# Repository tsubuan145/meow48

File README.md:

Build guide(Japanese only)
https://note.com/tsubuan_145/n/n66479057b7cb

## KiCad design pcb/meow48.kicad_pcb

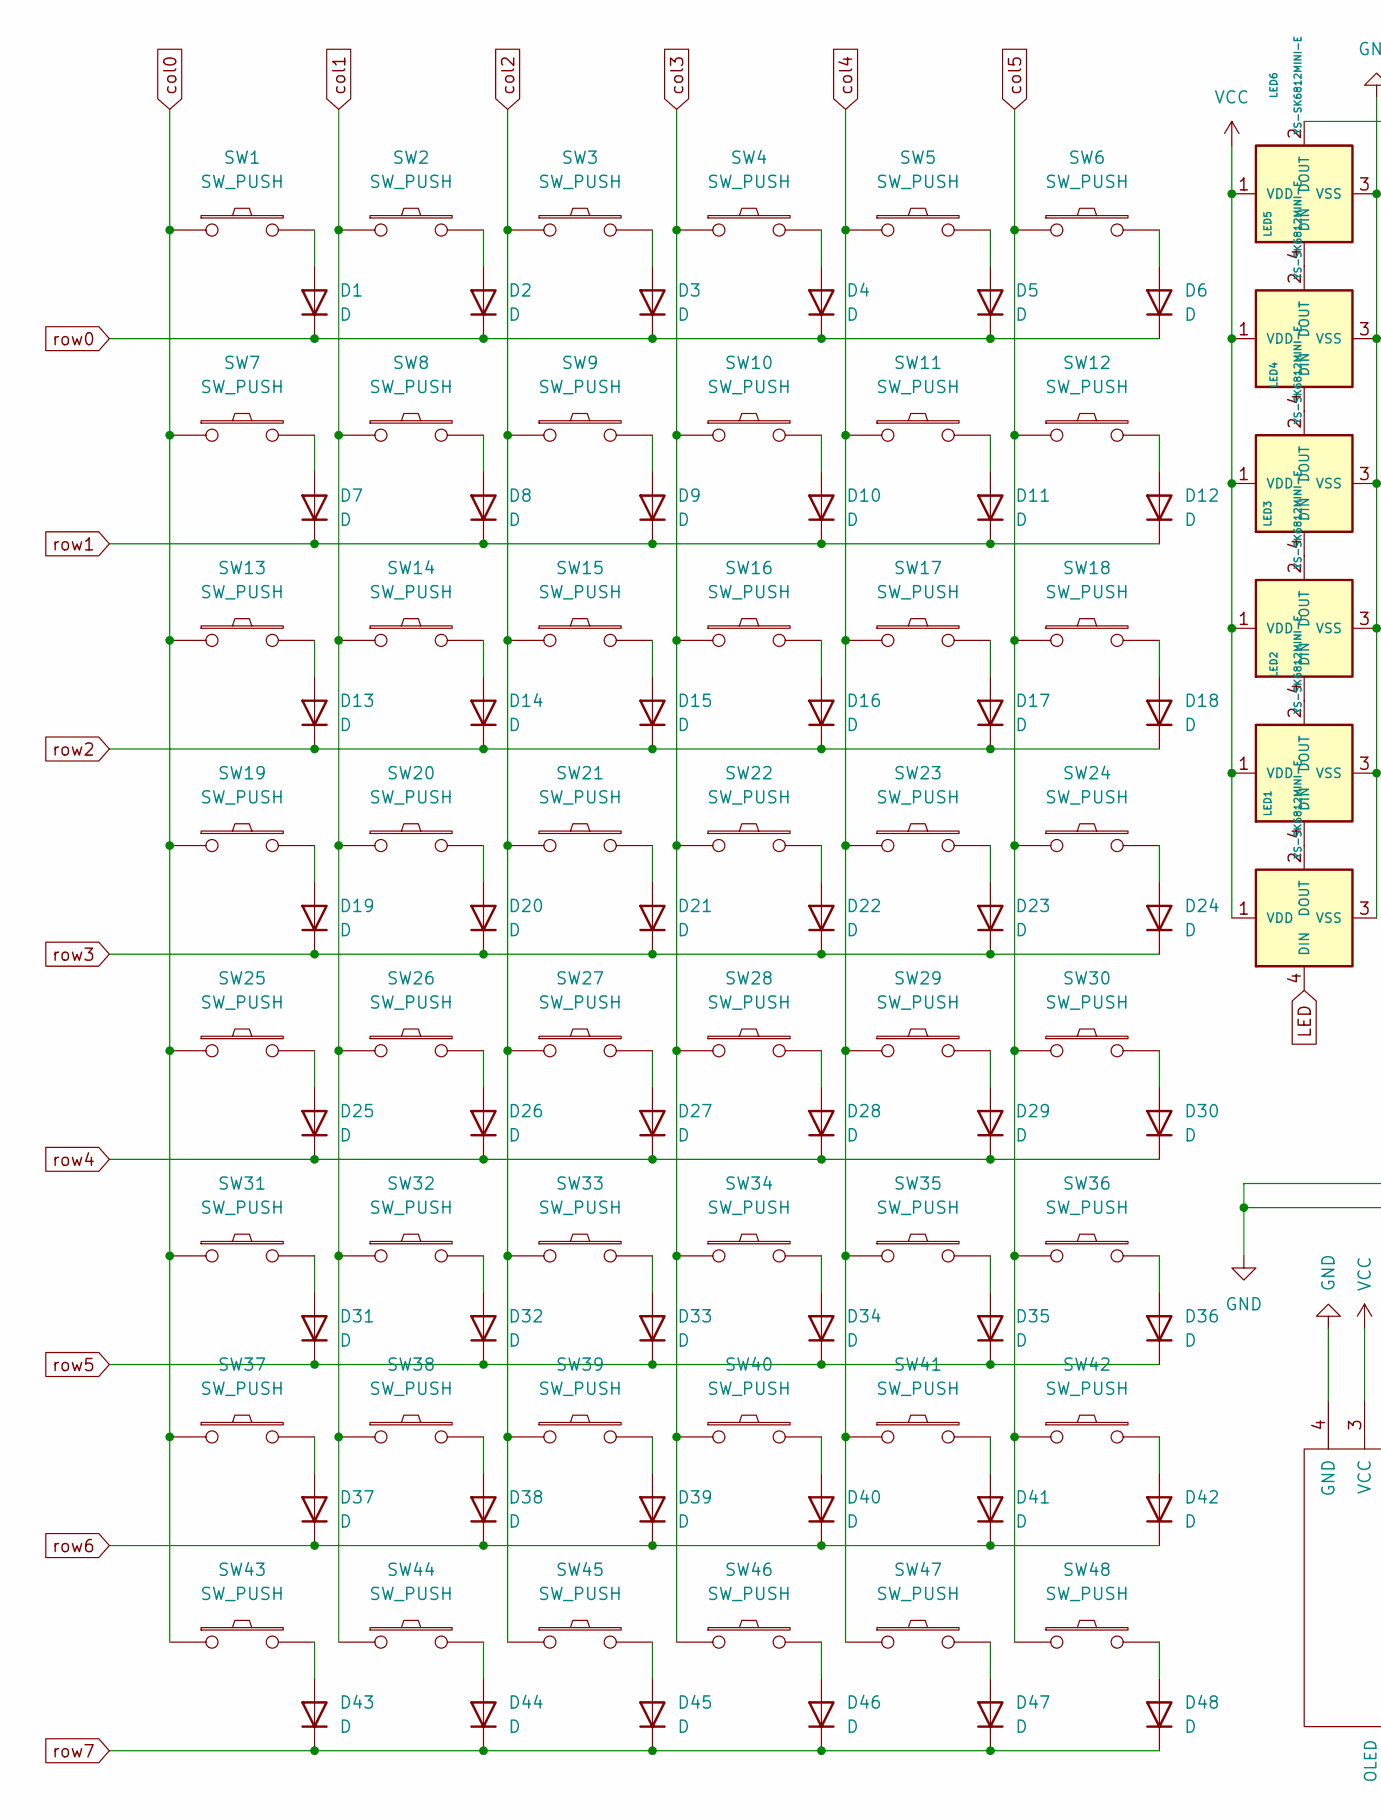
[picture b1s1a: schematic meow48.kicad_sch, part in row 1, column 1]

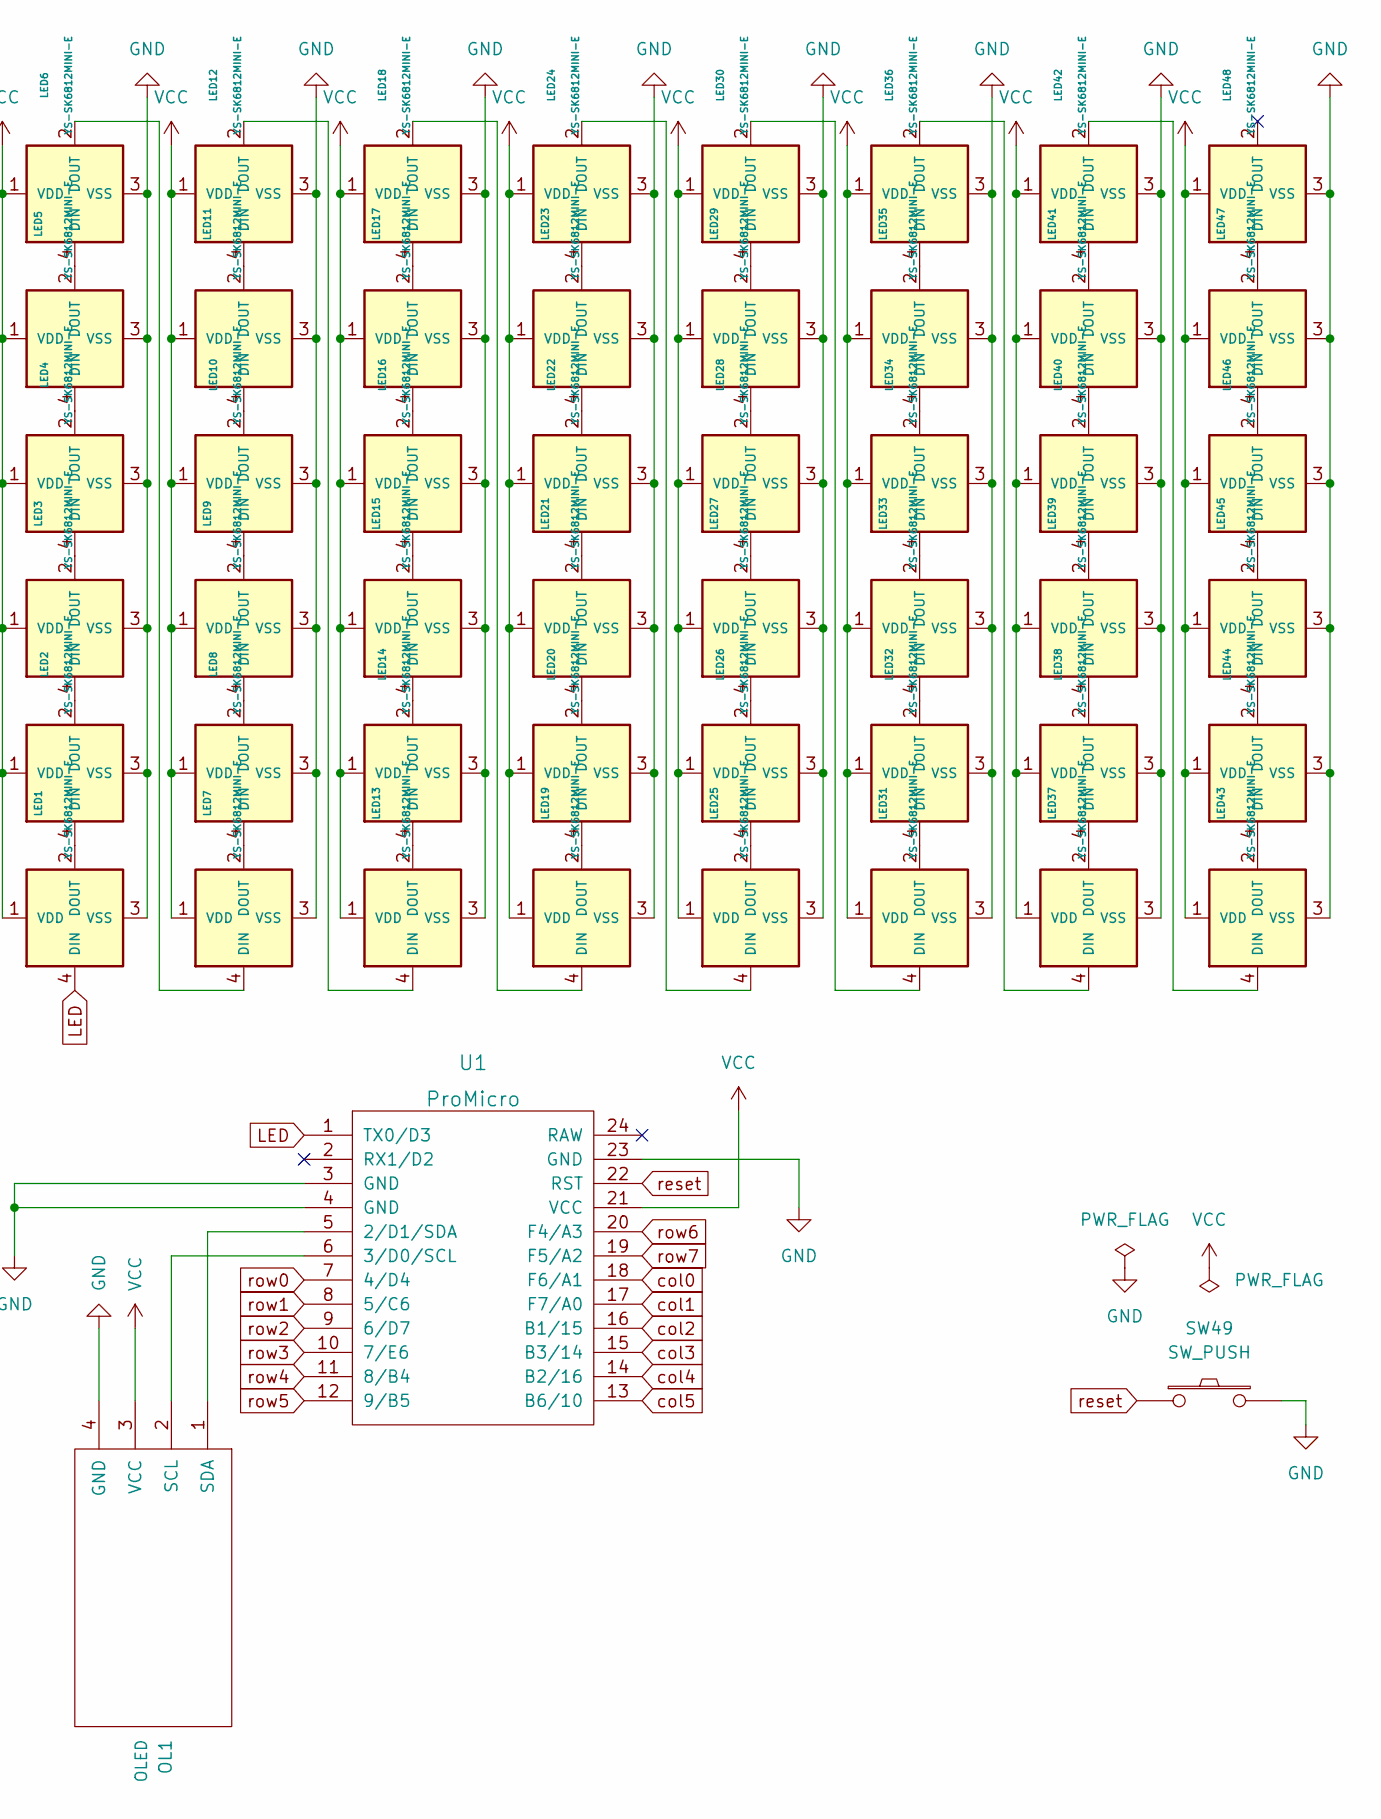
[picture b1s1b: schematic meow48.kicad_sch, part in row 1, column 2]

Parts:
D1, D2, D3, D4, D5, D6, D7, D8, D9, D10, D11, D12, D13, D14, D15, D16, D17, D18, D19, D20, D21, D22, D23, D24, D25, D26, D27, D28, D29, D30, D31, D32, D33, D34, D35, D36, D37, D38, D39, D40, D41, D42, D43, D44, D45, D46, D47, D48: D; Diode_SMD
LED1, LED2, LED3, LED4, LED5, LED6, LED7, LED8, LED9, LED10, LED11, LED12, LED13, LED14, LED15, LED16, LED17, LED18, LED19, LED20, LED21, LED22, LED23, LED24, LED25, LED26, LED27, LED28, LED29, LED30, LED31, LED32, LED33, LED34, LED35, LED36, LED37, LED38, LED39, LED40, LED41, LED42, LED43, LED44, LED45, LED46, LED47, LED48: YS-SK6812MINI-E; SK6812-MINI-E
OL1: OLED
SW1, SW2, SW3, SW4, SW5, SW6, SW7, SW8, SW9, SW10, SW11, SW12, SW13, SW14, SW15, SW16, SW17, SW18, SW19, SW20, SW21, SW22, SW23, SW25, SW26, SW27, SW28, SW29, SW30, SW31, SW32, SW33, SW34, SW35, SW36, SW37, SW38, SW39, SW41, SW42, SW43, SW44, SW46, SW47, SW48: SW_PUSH; Choc_Hotswap_1u_Small1_rev2
SW24, SW40, SW45: SW_PUSH; Choc_Hotswap_2u_Stab_rev2
SW49: SW_PUSH; ResetSW_1side
U1: ProMicro; ProMicro_v2_1side

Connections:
GND: LED1.3 (VSS), LED2.3 (VSS), LED3.3 (VSS), LED4.3 (VSS), LED5.3 (VSS), LED6.3 (VSS), LED7.3 (VSS), LED8.3 (VSS), LED9.3 (VSS), LED10.3 (VSS), LED11.3 (VSS), LED12.3 (VSS), LED13.3 (VSS), LED14.3 (VSS), LED15.3 (VSS), LED16.3 (VSS), LED17.3 (VSS), LED18.3 (VSS), LED19.3 (VSS), LED20.3 (VSS), LED21.3 (VSS), LED22.3 (VSS), LED23.3 (VSS), LED24.3 (VSS), LED25.3 (VSS), LED26.3 (VSS), LED27.3 (VSS), LED28.3 (VSS), LED29.3 (VSS), LED30.3 (VSS), LED31.3 (VSS), LED32.3 (VSS), LED33.3 (VSS), LED34.3 (VSS), LED35.3 (VSS), LED36.3 (VSS), LED37.3 (VSS), LED38.3 (VSS), LED39.3 (VSS), LED40.3 (VSS), LED41.3 (VSS), LED42.3 (VSS), LED43.3 (VSS), LED44.3 (VSS), LED45.3 (VSS), LED46.3 (VSS), LED47.3 (VSS), LED48.3 (VSS), OL1.4 (GND), SW49.2, U1.3 (GND), U1.4 (GND), U1.23 (GND)
LED: LED1.4 (DIN), U1.1 (TX0/D3)
unnamed: D1.2 (A), SW1.2
unnamed: D2.2 (A), SW2.2
unnamed: D3.2 (A), SW3.2
unnamed: D4.2 (A), SW4.2
unnamed: D5.2 (A), SW5.2
unnamed: D6.2 (A), SW6.2
unnamed: D7.2 (A), SW7.2
unnamed: D8.2 (A), SW8.2
unnamed: D9.2 (A), SW9.2
unnamed: D10.2 (A), SW10.2
unnamed: D11.2 (A), SW11.2
unnamed: D12.2 (A), SW12.2
unnamed: D13.2 (A), SW13.2
unnamed: D14.2 (A), SW14.2
unnamed: D15.2 (A), SW15.2
unnamed: D16.2 (A), SW16.2
unnamed: D17.2 (A), SW17.2
unnamed: D18.2 (A), SW18.2
unnamed: D19.2 (A), SW19.2
unnamed: D20.2 (A), SW20.2
unnamed: D21.2 (A), SW21.2
unnamed: D22.2 (A), SW22.2
unnamed: D23.2 (A), SW23.2
unnamed: D24.2 (A), SW24.2
unnamed: D25.2 (A), SW25.2
unnamed: D26.2 (A), SW26.2
unnamed: D27.2 (A), SW27.2
unnamed: D28.2 (A), SW28.2
unnamed: D29.2 (A), SW29.2
unnamed: D30.2 (A), SW30.2
unnamed: D31.2 (A), SW31.2
unnamed: D32.2 (A), SW32.2
unnamed: D33.2 (A), SW33.2
unnamed: D34.2 (A), SW34.2
unnamed: D35.2 (A), SW35.2
unnamed: D36.2 (A), SW36.2
unnamed: D37.2 (A), SW37.2
unnamed: D38.2 (A), SW38.2
unnamed: D39.2 (A), SW39.2
unnamed: D40.2 (A), SW40.2
unnamed: D41.2 (A), SW41.2
unnamed: D42.2 (A), SW42.2
unnamed: D43.2 (A), SW43.2
unnamed: D44.2 (A), SW44.2
unnamed: D45.2 (A), SW45.2
unnamed: D46.2 (A), SW46.2
unnamed: D47.2 (A), SW47.2
unnamed: D48.2 (A), SW48.2
unnamed: LED1.2 (DOUT), LED2.4 (DIN)
unnamed: LED2.2 (DOUT), LED3.4 (DIN)
unnamed: LED3.2 (DOUT), LED4.4 (DIN)
unnamed: LED4.2 (DOUT), LED5.4 (DIN)
unnamed: LED5.2 (DOUT), LED6.4 (DIN)
unnamed: LED6.2 (DOUT), LED7.4 (DIN)
unnamed: LED7.2 (DOUT), LED8.4 (DIN)
unnamed: LED8.2 (DOUT), LED9.4 (DIN)
unnamed: LED10.2 (DOUT), LED11.4 (DIN)
unnamed: LED9.2 (DOUT), LED10.4 (DIN)
unnamed: LED11.2 (DOUT), LED12.4 (DIN)
unnamed: LED12.2 (DOUT), LED13.4 (DIN)
unnamed: LED13.2 (DOUT), LED14.4 (DIN)
unnamed: LED14.2 (DOUT), LED15.4 (DIN)
unnamed: LED15.2 (DOUT), LED16.4 (DIN)
unnamed: LED16.2 (DOUT), LED17.4 (DIN)
unnamed: LED17.2 (DOUT), LED18.4 (DIN)
unnamed: LED18.2 (DOUT), LED19.4 (DIN)
unnamed: LED19.2 (DOUT), LED20.4 (DIN)
unnamed: LED20.2 (DOUT), LED21.4 (DIN)
unnamed: LED21.2 (DOUT), LED22.4 (DIN)
unnamed: LED22.2 (DOUT), LED23.4 (DIN)
unnamed: LED23.2 (DOUT), LED24.4 (DIN)
unnamed: LED24.2 (DOUT), LED25.4 (DIN)
unnamed: LED25.2 (DOUT), LED26.4 (DIN)
unnamed: LED26.2 (DOUT), LED27.4 (DIN)
unnamed: LED27.2 (DOUT), LED28.4 (DIN)
unnamed: LED28.2 (DOUT), LED29.4 (DIN)
unnamed: LED29.2 (DOUT), LED30.4 (DIN)
unnamed: LED30.2 (DOUT), LED31.4 (DIN)
unnamed: LED31.2 (DOUT), LED32.4 (DIN)
unnamed: LED32.2 (DOUT), LED33.4 (DIN)
unnamed: LED33.2 (DOUT), LED34.4 (DIN)
unnamed: LED34.2 (DOUT), LED35.4 (DIN)
unnamed: LED35.2 (DOUT), LED36.4 (DIN)
unnamed: LED36.2 (DOUT), LED37.4 (DIN)
unnamed: LED37.2 (DOUT), LED38.4 (DIN)
unnamed: LED38.2 (DOUT), LED39.4 (DIN)
unnamed: LED39.2 (DOUT), LED40.4 (DIN)
unnamed: LED40.2 (DOUT), LED41.4 (DIN)
unnamed: LED41.2 (DOUT), LED42.4 (DIN)
unnamed: LED42.2 (DOUT), LED43.4 (DIN)
unnamed: LED43.2 (DOUT), LED44.4 (DIN)
unnamed: LED44.2 (DOUT), LED45.4 (DIN)
unnamed: LED45.2 (DOUT), LED46.4 (DIN)
unnamed: LED46.2 (DOUT), LED47.4 (DIN)
unnamed: LED47.2 (DOUT), LED48.4 (DIN)
unnamed: OL1.1 (SDA), U1.5 (2/D1/SDA)
unnamed: OL1.2 (SCL), U1.6 (3/D0/SCL)
VCC: LED1.1 (VDD), LED2.1 (VDD), LED3.1 (VDD), LED4.1 (VDD), LED5.1 (VDD), LED6.1 (VDD), LED7.1 (VDD), LED8.1 (VDD), LED9.1 (VDD), LED10.1 (VDD), LED11.1 (VDD), LED12.1 (VDD), LED13.1 (VDD), LED14.1 (VDD), LED15.1 (VDD), LED16.1 (VDD), LED17.1 (VDD), LED18.1 (VDD), LED19.1 (VDD), LED20.1 (VDD), LED21.1 (VDD), LED22.1 (VDD), LED23.1 (VDD), LED24.1 (VDD), LED25.1 (VDD), LED26.1 (VDD), LED27.1 (VDD), LED28.1 (VDD), LED29.1 (VDD), LED30.1 (VDD), LED31.1 (VDD), LED32.1 (VDD), LED33.1 (VDD), LED34.1 (VDD), LED35.1 (VDD), LED36.1 (VDD), LED37.1 (VDD), LED38.1 (VDD), LED39.1 (VDD), LED40.1 (VDD), LED41.1 (VDD), LED42.1 (VDD), LED43.1 (VDD), LED44.1 (VDD), LED45.1 (VDD), LED46.1 (VDD), LED47.1 (VDD), LED48.1 (VDD), OL1.3 (VCC), U1.21 (VCC)
col0: SW1.1, SW7.1, SW13.1, SW19.1, SW25.1, SW31.1, SW37.1, SW43.1, U1.18 (F6/A1)
col1: SW2.1, SW8.1, SW14.1, SW20.1, SW26.1, SW32.1, SW38.1, SW44.1, U1.17 (F7/A0)
col2: SW3.1, SW9.1, SW15.1, SW21.1, SW27.1, SW33.1, SW39.1, SW45.1, U1.16 (B1/15)
col3: SW4.1, SW10.1, SW16.1, SW22.1, SW28.1, SW34.1, SW40.1, SW46.1, U1.15 (B3/14)
col4: SW5.1, SW11.1, SW17.1, SW23.1, SW29.1, SW35.1, SW41.1, SW47.1, U1.14 (B2/16)
col5: SW6.1, SW12.1, SW18.1, SW24.1, SW30.1, SW36.1, SW42.1, SW48.1, U1.13 (B6/10)
reset: SW49.1, U1.22 (RST)
row0: D1.1 (K), D2.1 (K), D3.1 (K), D4.1 (K), D5.1 (K), D6.1 (K), U1.7 (4/D4)
row1: D7.1 (K), D8.1 (K), D9.1 (K), D10.1 (K), D11.1 (K), D12.1 (K), U1.8 (5/C6)
row2: D13.1 (K), D14.1 (K), D15.1 (K), D16.1 (K), D17.1 (K), D18.1 (K), U1.9 (6/D7)
row3: D19.1 (K), D20.1 (K), D21.1 (K), D22.1 (K), D23.1 (K), D24.1 (K), U1.10 (7/E6)
row4: D25.1 (K), D26.1 (K), D27.1 (K), D28.1 (K), D29.1 (K), D30.1 (K), U1.11 (8/B4)
row5: D31.1 (K), D32.1 (K), D33.1 (K), D34.1 (K), D35.1 (K), D36.1 (K), U1.12 (9/B5)
row6: D37.1 (K), D38.1 (K), D39.1 (K), D40.1 (K), D41.1 (K), D42.1 (K), U1.20 (F4/A3)
row7: D43.1 (K), D44.1 (K), D45.1 (K), D46.1 (K), D47.1 (K), D48.1 (K), U1.19 (F5/A2)

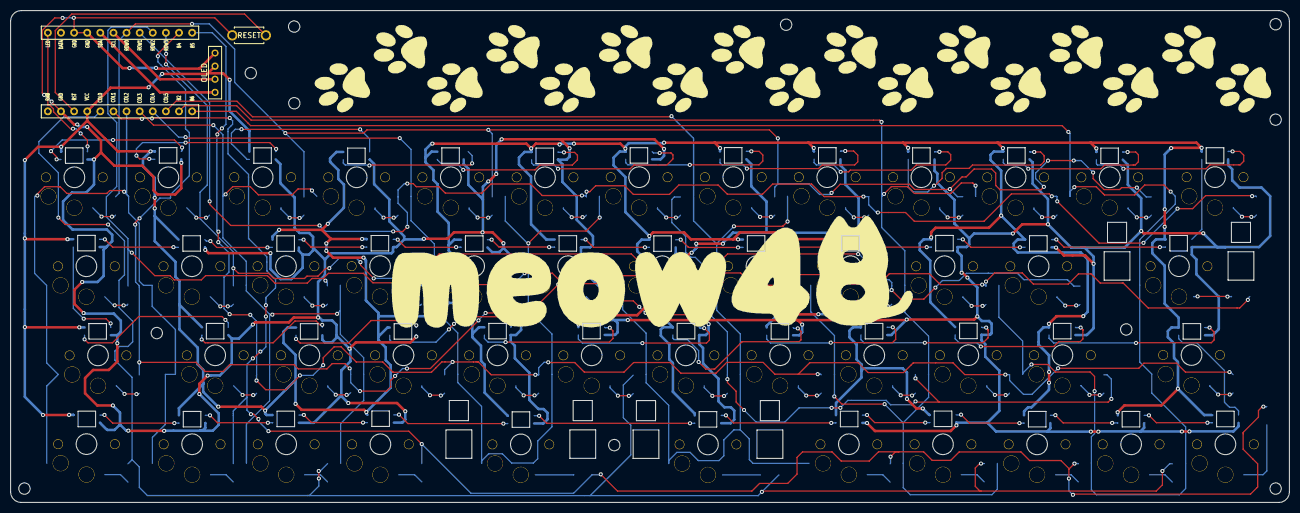
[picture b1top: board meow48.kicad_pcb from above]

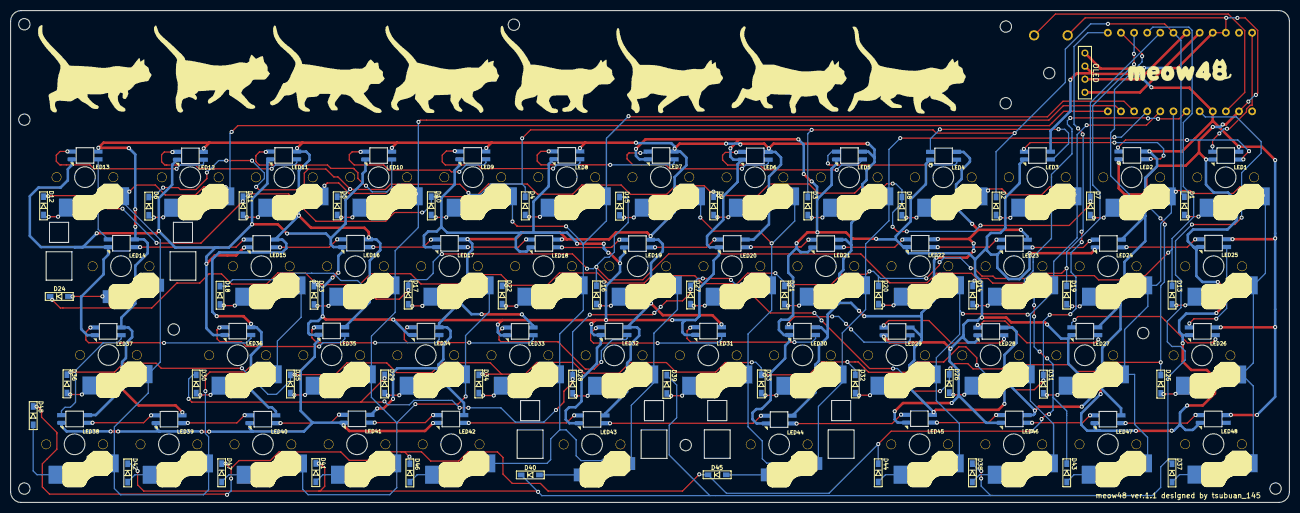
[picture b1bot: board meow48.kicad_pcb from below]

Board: 2 copper layers, 247.6 x 95.2 mm, 158 parts (48 on the bottom side), 115 nets.

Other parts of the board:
Ref**: Val**; m2_Screw_Hole
Ref**#2, Ref**#3, Ref**#4, Ref**#5, Ref**#6, Ref**#7, Ref**#8, Ref**#9, Ref**#10, Ref**#11: Val**; m2_Screw_Hole

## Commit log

2022-11-20 [Keyboard]meow48
    CRLF > LF fixed
2022-11-20 meow.h fixed
2022-11-20 keymap.c and rules.mk fixed
2022-11-20 Fixed
2022-11-28 Update keymap.c
    Fixed
2022-11-28 Update config.h
    Fixed
2022-11-30 OLED bug fixed
2022-11-30 Update config.h
    Add USB Device descriptor parameter
2022-12-01 Update vid
2022-12-01 vid fixed
2022-12-09 ProMicro plate and bottom plate
    Acrylic board data has been added.
2022-12-14 Bottom plate fixed
2022-12-14 Add PCB files upload
2022-12-14 Add gerber files upload
2022-12-20 Gerber files update ver.1.1
2022-12-20 Update README.md
    Add the build guide
